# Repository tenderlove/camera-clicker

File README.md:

# Camera Clicker

This project is a dedicated WiFi client and remote shutter for Olympus OM-D cameras.
It simply connects to the camera, and then you can use the button to fire the camera shutter.
I've only tested this with my OM-D E-M5 Mark III camera, but I believe it will work with any OM-D camera that uses WiFi for its remote shutter application.

In this repository, you'll find [schematics and PCB designs](pcb), [stl files](housing), and the [firmware](firmware) you need.

## Hardware

The hardware is based around the ESP32.  It uses an [LiFePO4 battery](https://www.digikey.com/en/products/detail/zeus-battery-products/PCIFR18650-1500/9828824) to provide power to the ESP32.
I chose this battery because it provides 3.2v which means I don't need a voltage regulator for the ESP32.
The schematic integrates a recharging circuit, so you can recharge the battery via USB C.

Below are the necessary parts:

| Quantity | Part | Value | Size |
| -------- | ---- | ---- | ----- |
| 1 | [Battery Holder](https://www.digikey.com/en/products/detail/keystone-electronics/1042/2745668) |  | BatteryHolder_Keystone_1042_1x18650 |
| 1 | [Battery](https://www.digikey.com/en/products/detail/zeus-battery-products/PCIFR18650-1500/9828824) |  |  |
| 2 | Capacitor | 1uf | 0402 |
| 1 | Capacitor | 22uf | 1206 |
| 1 | Capacitor | 0.1uf | 1206 |
| 2 | LED |  | 1206 |
| 1 | [USB C connector](https://www.digikey.com/en/products/detail/amphenol-cs-fci/10164359-00011LF/18443702) |  | USB_C_Receptacle_Amphenol_10164359-3A |
| 1 | Resistor | 82k | 0402 |
| 1 | Resistor | 3k | 0402 |
| 4 | Resistor | 10k | 1206 |
| 1 | Resistor | 70k | 0402 |
| 1 | Resistor | 2.3k | 0402 |
| 2 | Resistor | 5.1k | 1206 |
| 1 | [Power Switch](https://www.digikey.com/en/products/detail/te-connectivity-alcoswitch-switches/1825232-1/4021554) |  |  |
| 2 | [Programming Switches](https://www.digikey.com/en/products/detail/c-k/PTS526-SK15-SMTR2-LFS/10056626) |  | SW_SPST_PTS526 |
| 1 | [Double Action Switch](https://www.digikey.com/en/products/detail/panasonic-electronic-components/EVP-AXBA1A/4930566) |  | EVPAX-A1A |
| 1 | NTC Thermistor | 10k NTC | 1206 |
| 1 | [Battery Charger](https://www.digikey.com/en/products/detail/texas-instruments/BQ25170DSGR/14124032) | BQ25170 | WSON-8-1EP_2x2mm_P0.5mm_EP0.9x1.6mm |
| 1 | [ESP32](https://www.digikey.com/en/products/detail/espressif-systems/ESP32-MINI-1-N4/13532111) |  |  |

You'll find the gerber files in the [pcb folder](pcb).
Also, I used 10k resistors for the LEDs, but I think it made the LEDs too dim, so maybe 1k is better.
The LEDs are used to indicate charging status, so I don't think they actually matter too much.

Here's a couple photos of the finished PCB:

## Firmware

The firmware is in the [firmware](firmware) folder.  It's a standard [ESP IDF](https://github.com/espressif/esp-idf) project.
In order to flash the ESP32, I used a [POGO Pin Clip](https://www.adafruit.com/product/5433) connected to a [USB to Serial](https://www.sparkfun.com/products/12731) board.

Once you have `esp-idf` installed, you can install the firmware like this:

```
$ idf.py build flash
```

Of course, make sure to press the BOOT and RST buttons to put the ESP32 in to programming mode.

## Housing

You can find STL files for the housing in the [housing](housing) folder.
Just print [`top.stl`](housing/top.stl) and [`bottom.stl`](housing/bottom.stl) and the PCB should fit inside.
The housing requires four M2 x 25mm bolts, and four 4mm hex nuts.

The PCB should fit in the housing like this:

## Using the Project

When you first turn the clicker on, it will create a WiFi hotspot with the SSID `CameraClicker` and the password `cameraclicker`.

My recommendation is to:

1. Turn on the camera, then enable WiFi client mode
2. Turn on the camera clicker
3. Connect to the camera clicker with your phone
4. Configure the camera clicker with the camera's WiFi settings (they will be displayed on the camera)
5. Use it!

The camera clicker will remember the camera's WiFi connection information, so you only need to configure it once.
If it can't connect to the camera for any reason, it will eventually start the WiFi hotspot again so that you can reconfigure it.

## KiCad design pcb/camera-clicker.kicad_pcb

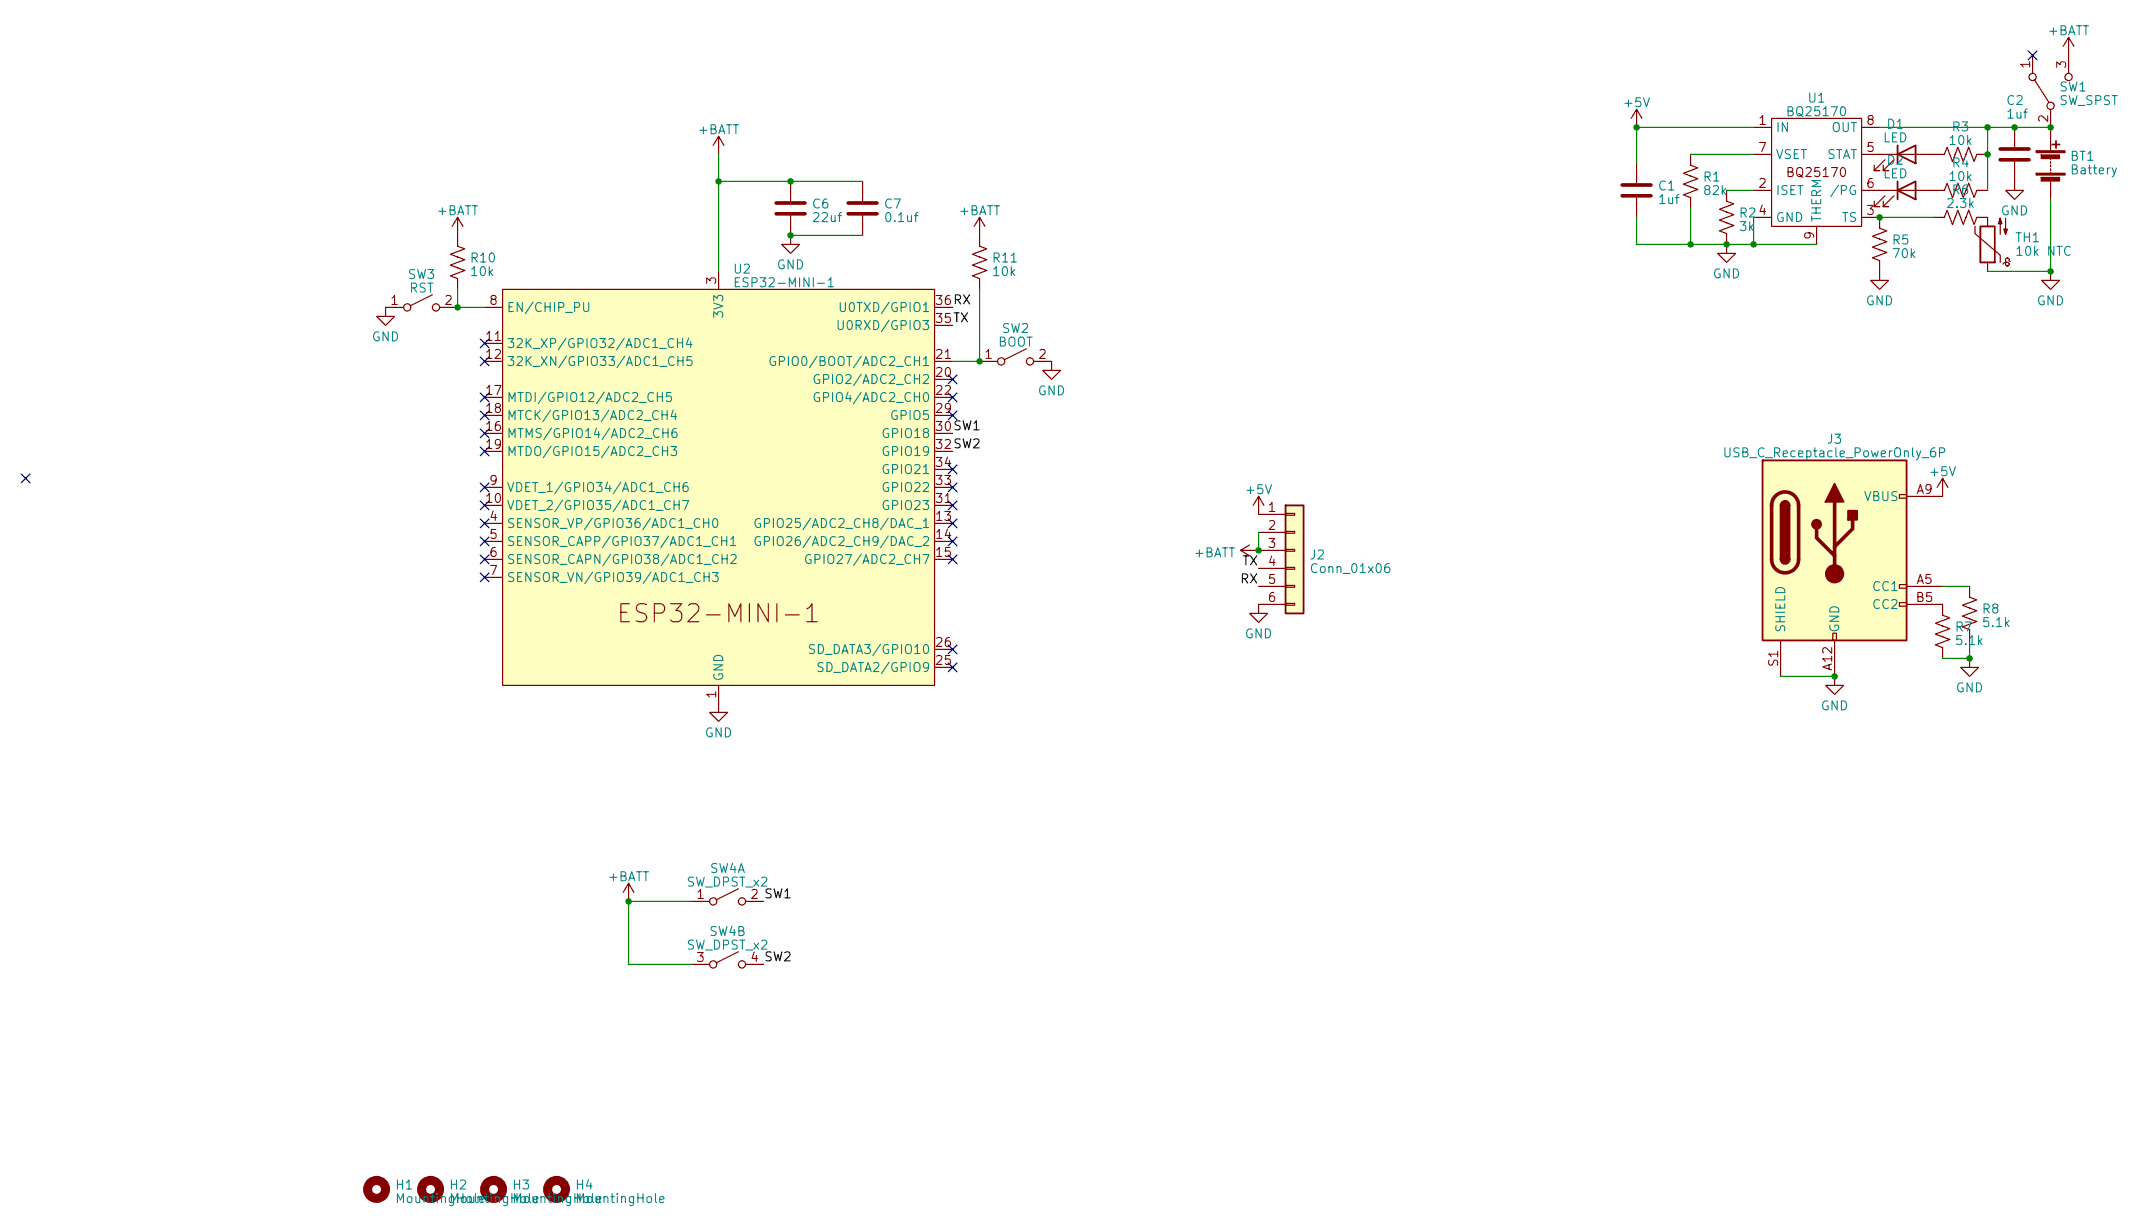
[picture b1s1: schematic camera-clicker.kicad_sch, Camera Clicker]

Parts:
BT1: Battery; BatteryHolder_Keystone_1042_1x18650
C1, C2: 1uf; C_0402_1005Metric
C6: 22uf; C_1206_3216Metric
C7: 0.1uf; C_1206_3216Metric
D1, D2: LED; LED_1206_3216Metric
H1, H2, H3, H4: MountingHole; MountingHole_2.2mm_M2
J2: Conn_01x06; PinHeader_1x06_P2.54mm_Vertical
J3: USB_C_Receptacle_PowerOnly_6P; USB_C_Receptacle_Amphenol_10164359-3A
R1: 82k; R_0402_1005Metric
R2: 3k; R_0402_1005Metric
R3, R4, R10, R11: 10k; R_1206_3216Metric
R5: 70k; R_0402_1005Metric
R6: 2.3k; R_0402_1005Metric
R7, R8: 5.1k; R_1206_3216Metric
SW1: SW_SPST; SW_CuK_OS102011MA1QN1_SPDT_Angled
SW2: BOOT; SW_SPST_PTS526
SW3: RST; SW_SPST_PTS526
SW4: SW_DPST_x2; EVPAX-A1A
TH1: 10k NTC; R_1206_3216Metric_Pad1.30x1.75mm_HandSolder
U1: BQ25170; WSON-8-1EP_2x2mm_P0.5mm_EP0.9x1.6mm
U2: ESP32-MINI-1

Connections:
+5V: C1.1, J2.1, J3.A9 (VBUS), J3.B9 (VBUS), U1.1 (IN)
+BATT: C6.1, C7.1, J2.2, J2.3, R10.1, R11.1, SW1.3 (C), SW4.1 (A), SW4.3 (A), U2.3 (3V3)
/RX: J2.5, U2.36 (U0TXD/GPIO1)
/SW1: SW4.2 (B), U2.30 (GPIO18)
/SW2: SW4.4 (B), U2.32 (GPIO19)
/TX: J2.4, U2.35 (U0RXD/GPIO3)
GND: BT1.2 (-), C1.2, C2.2, C6.2, C7.2, J2.6, J3.A12 (GND), J3.B12 (GND), J3.S1 (SHIELD), R1.2, R2.2, R5.2, R7.2, R8.2, SW2.2 (B), SW3.1 (A), TH1.1, U1.4 (GND), U1.9 (THERM), U2.1 (GND), U2.2 (GND), U2.27 (GND), U2.38 (GND), U2.39 (GND), U2.40 (GND), U2.41 (GND), U2.42 (GND), U2.43 (GND), U2.44 (GND), U2.45 (GND), U2.46 (GND), U2.47 (GND), U2.48 (GND), U2.49 (GND), U2.50 (GND), U2.51 (GND), U2.52 (GND), U2.53 (GND), U2.54 (GND), U2.55 (GND)
unnamed: BT1.1 (+), C2.1, R3.2, R4.2, SW1.2 (B), U1.8 (OUT)
unnamed: D1.2 (A), R3.1
unnamed: D1.1 (K), U1.5 (STAT)
unnamed: D2.2 (A), R4.1
unnamed: D2.1 (K), U1.6 (/PG)
unnamed: J3.A5 (CC1), R8.1
unnamed: J3.B5 (CC2), R7.1
unnamed: R6.2, TH1.2
unnamed: R11.2, SW2.1 (A), U2.21 (GPIO0/BOOT/ADC2_CH1)
unnamed: R10.2, SW3.2 (B), U2.8 (EN/CHIP_PU)
unnamed: R2.1, U1.2 (ISET)
unnamed: R5.1, R6.1, U1.3 (TS)
unnamed: R1.1, U1.7 (VSET)

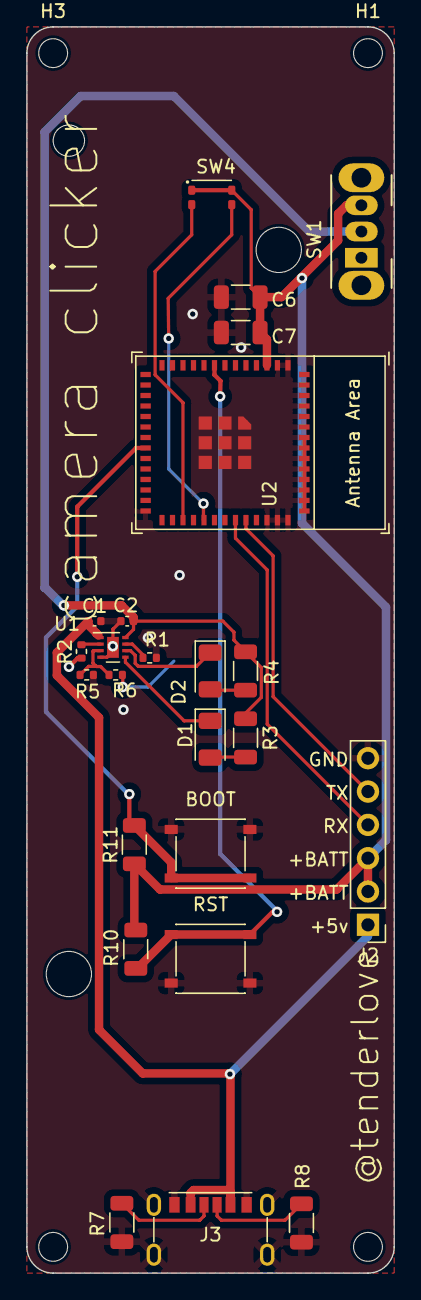
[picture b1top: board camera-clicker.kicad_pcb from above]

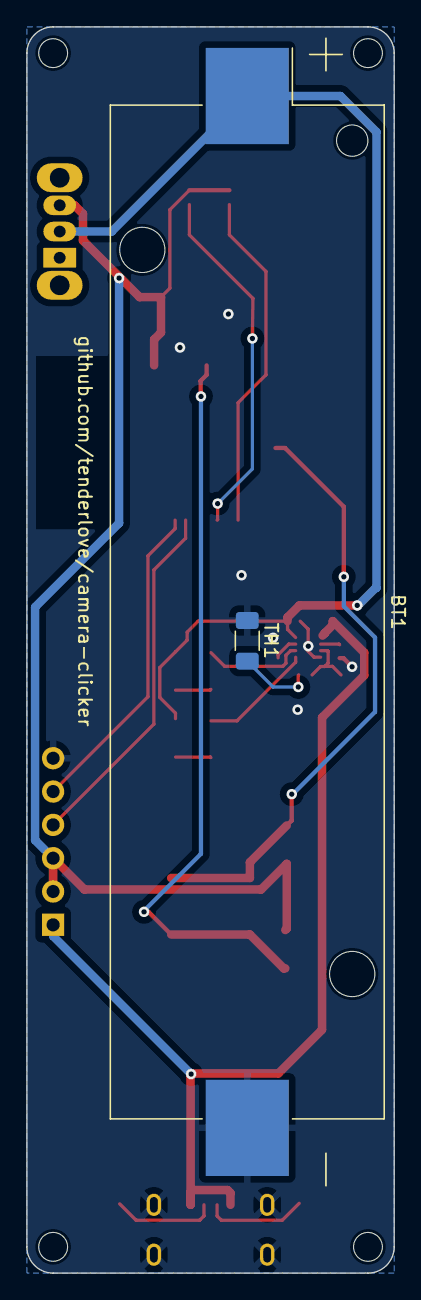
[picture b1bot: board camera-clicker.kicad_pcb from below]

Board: 2 copper layers, 28.0 x 95.0 mm, 30 parts (2 on the bottom side), 20 nets.

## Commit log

2023-05-21 initial
2023-05-22 adding wifi manager submodule
2023-05-23 building with wifi manager
2023-05-23 switching camera mode on connect
2023-05-23 buttons are working
2023-05-24 adding initial pcb stuff
2023-05-25 updating design
2023-05-31 first layout
2023-05-31 fixing position
2023-05-31 more pcb
2023-06-13 add configuration
2023-06-13 update pcb
2023-06-13 button is working
2023-06-14 refactor button presses
2023-06-14 add new switch footprint
2023-06-17 adding footprint for USB C receptacle
2023-06-17 new pcb design
2023-06-27 updating pcb
2023-06-27 initial case
2023-06-28 adding counter sunk holes, and bolt head holes
2023-06-28 adding makefile
2023-06-28 testing pushbutton and nut height
2023-06-29 2.1 was too small
2023-06-29 add a button
2023-06-29 Use a tab for the switch button
2023-06-29 More readme
2023-06-29 add license
2023-06-29 bigger images
2023-06-29 move info
2023-06-30 pull tab gap in to a variable

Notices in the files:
pcb/camera-clicker.kicad_pcb:
Apache-2.0 License
© Aaron Patterson
